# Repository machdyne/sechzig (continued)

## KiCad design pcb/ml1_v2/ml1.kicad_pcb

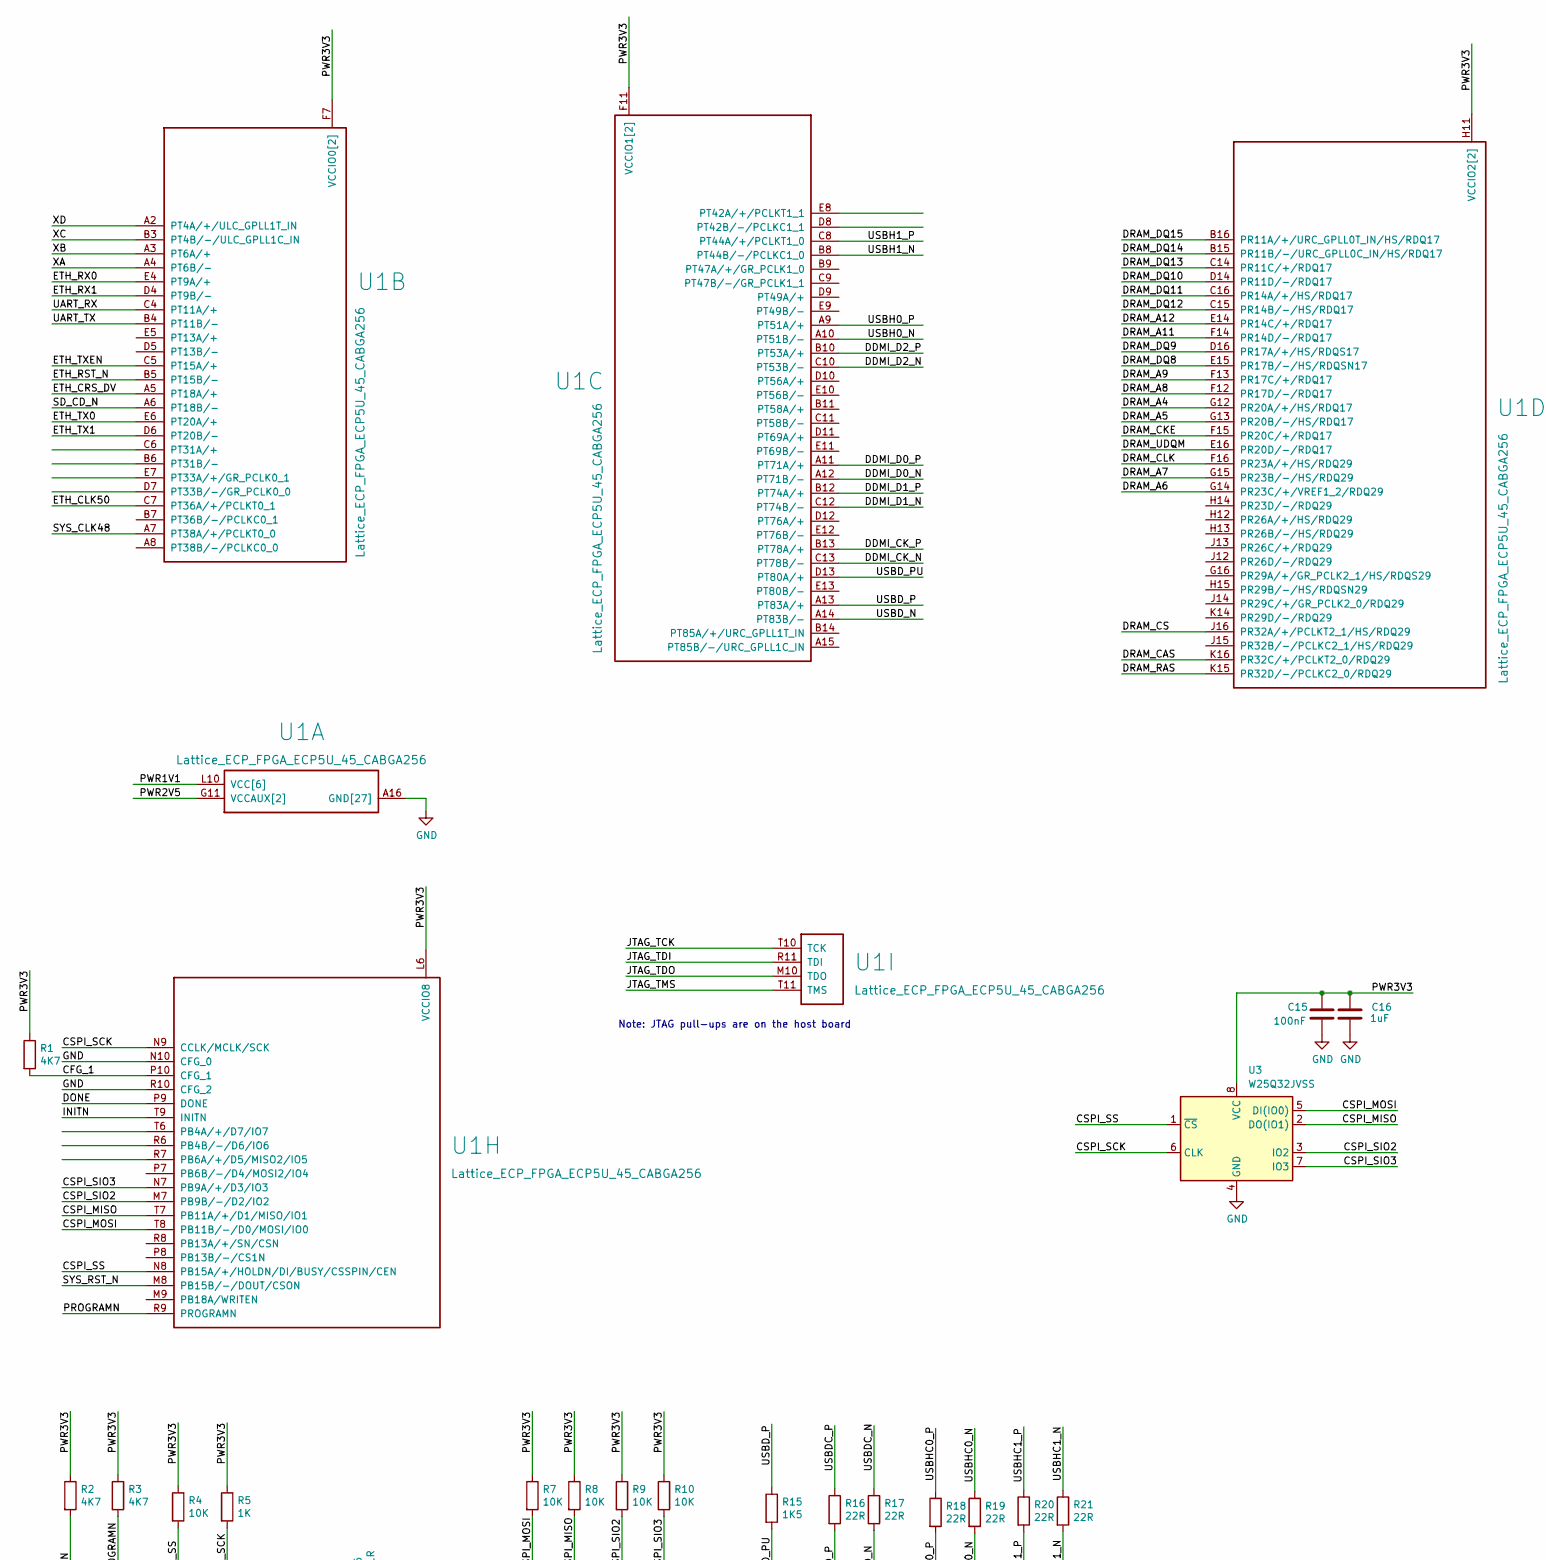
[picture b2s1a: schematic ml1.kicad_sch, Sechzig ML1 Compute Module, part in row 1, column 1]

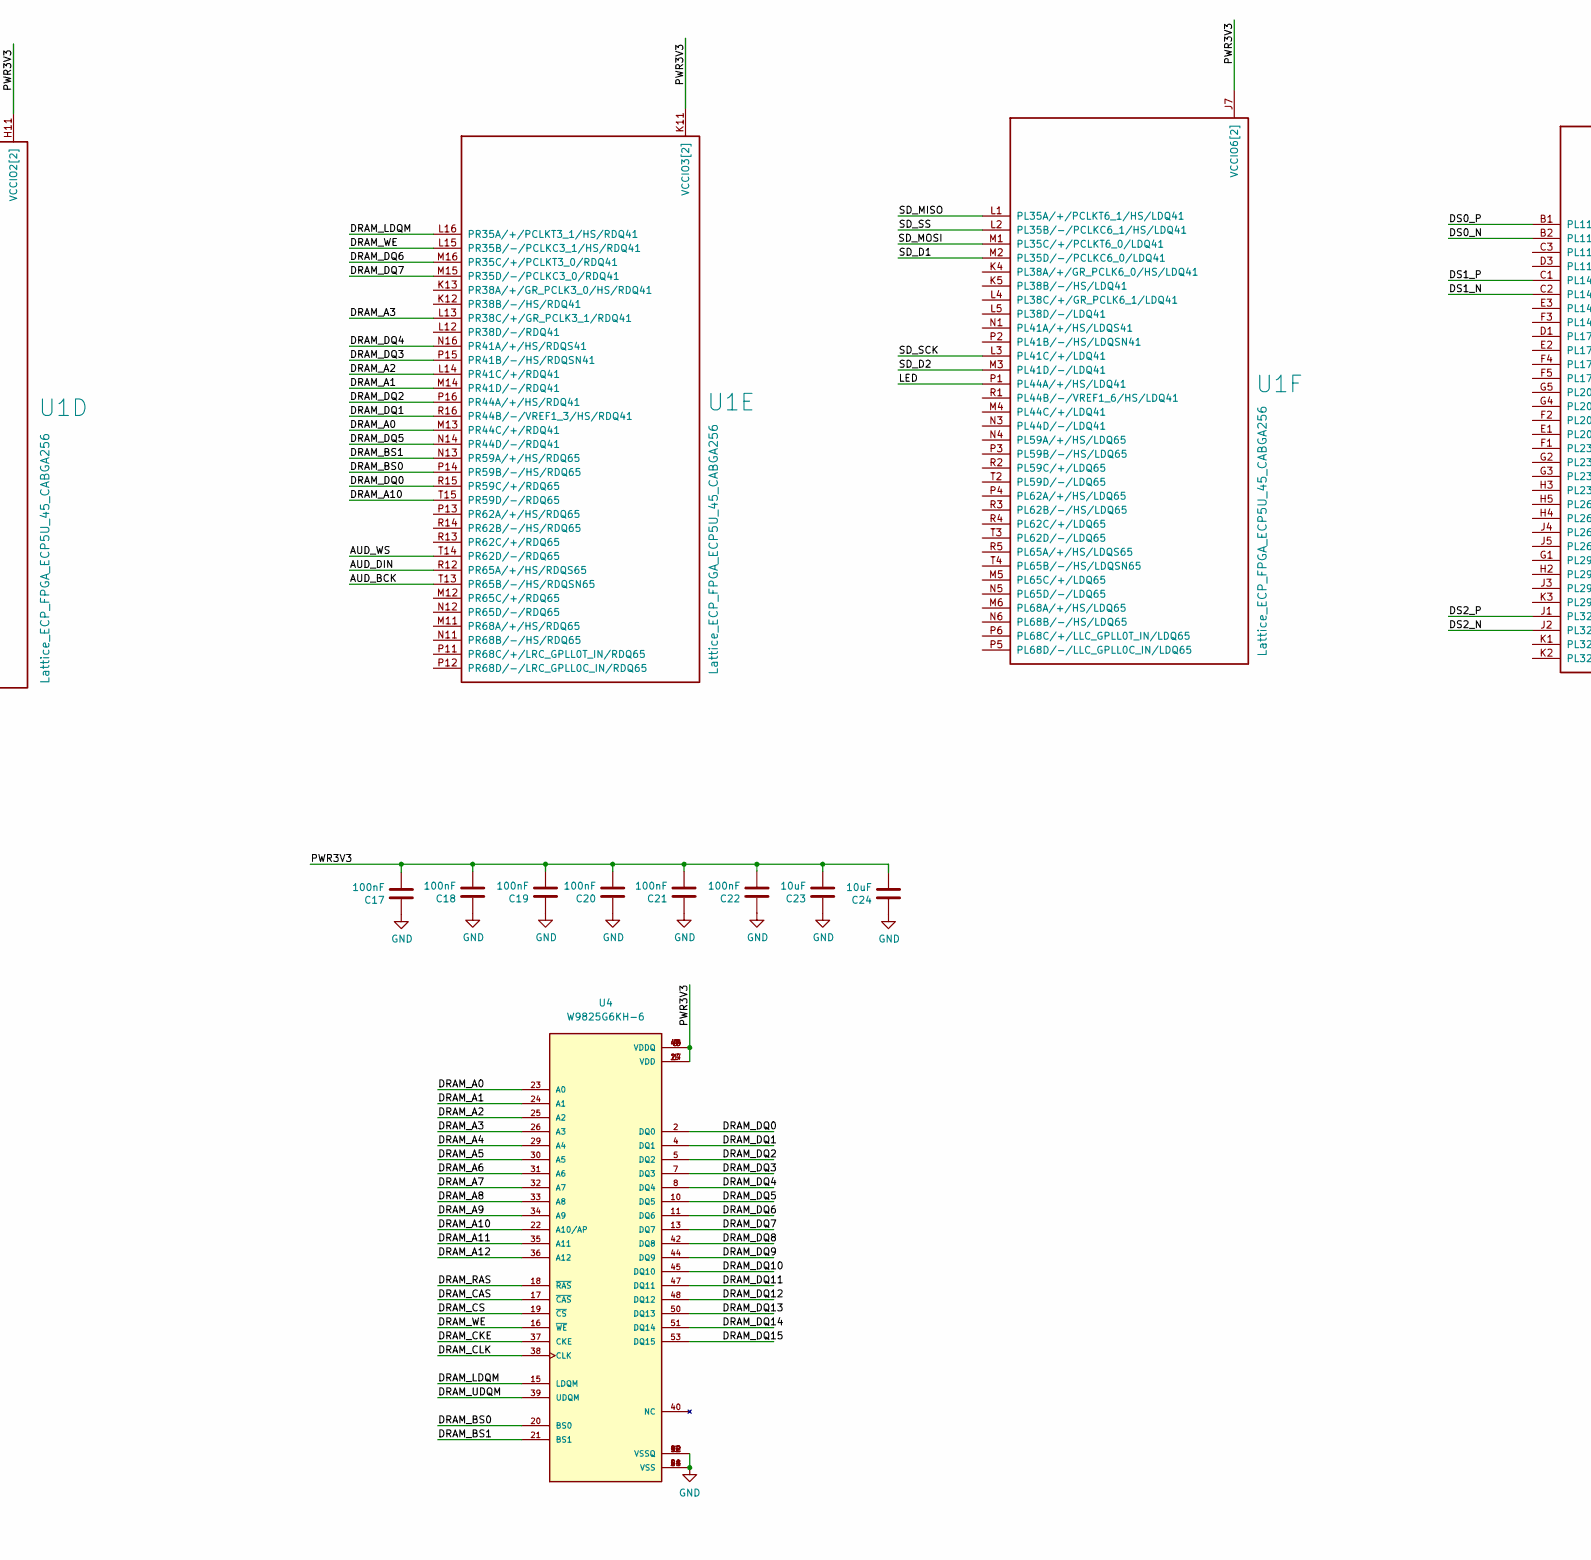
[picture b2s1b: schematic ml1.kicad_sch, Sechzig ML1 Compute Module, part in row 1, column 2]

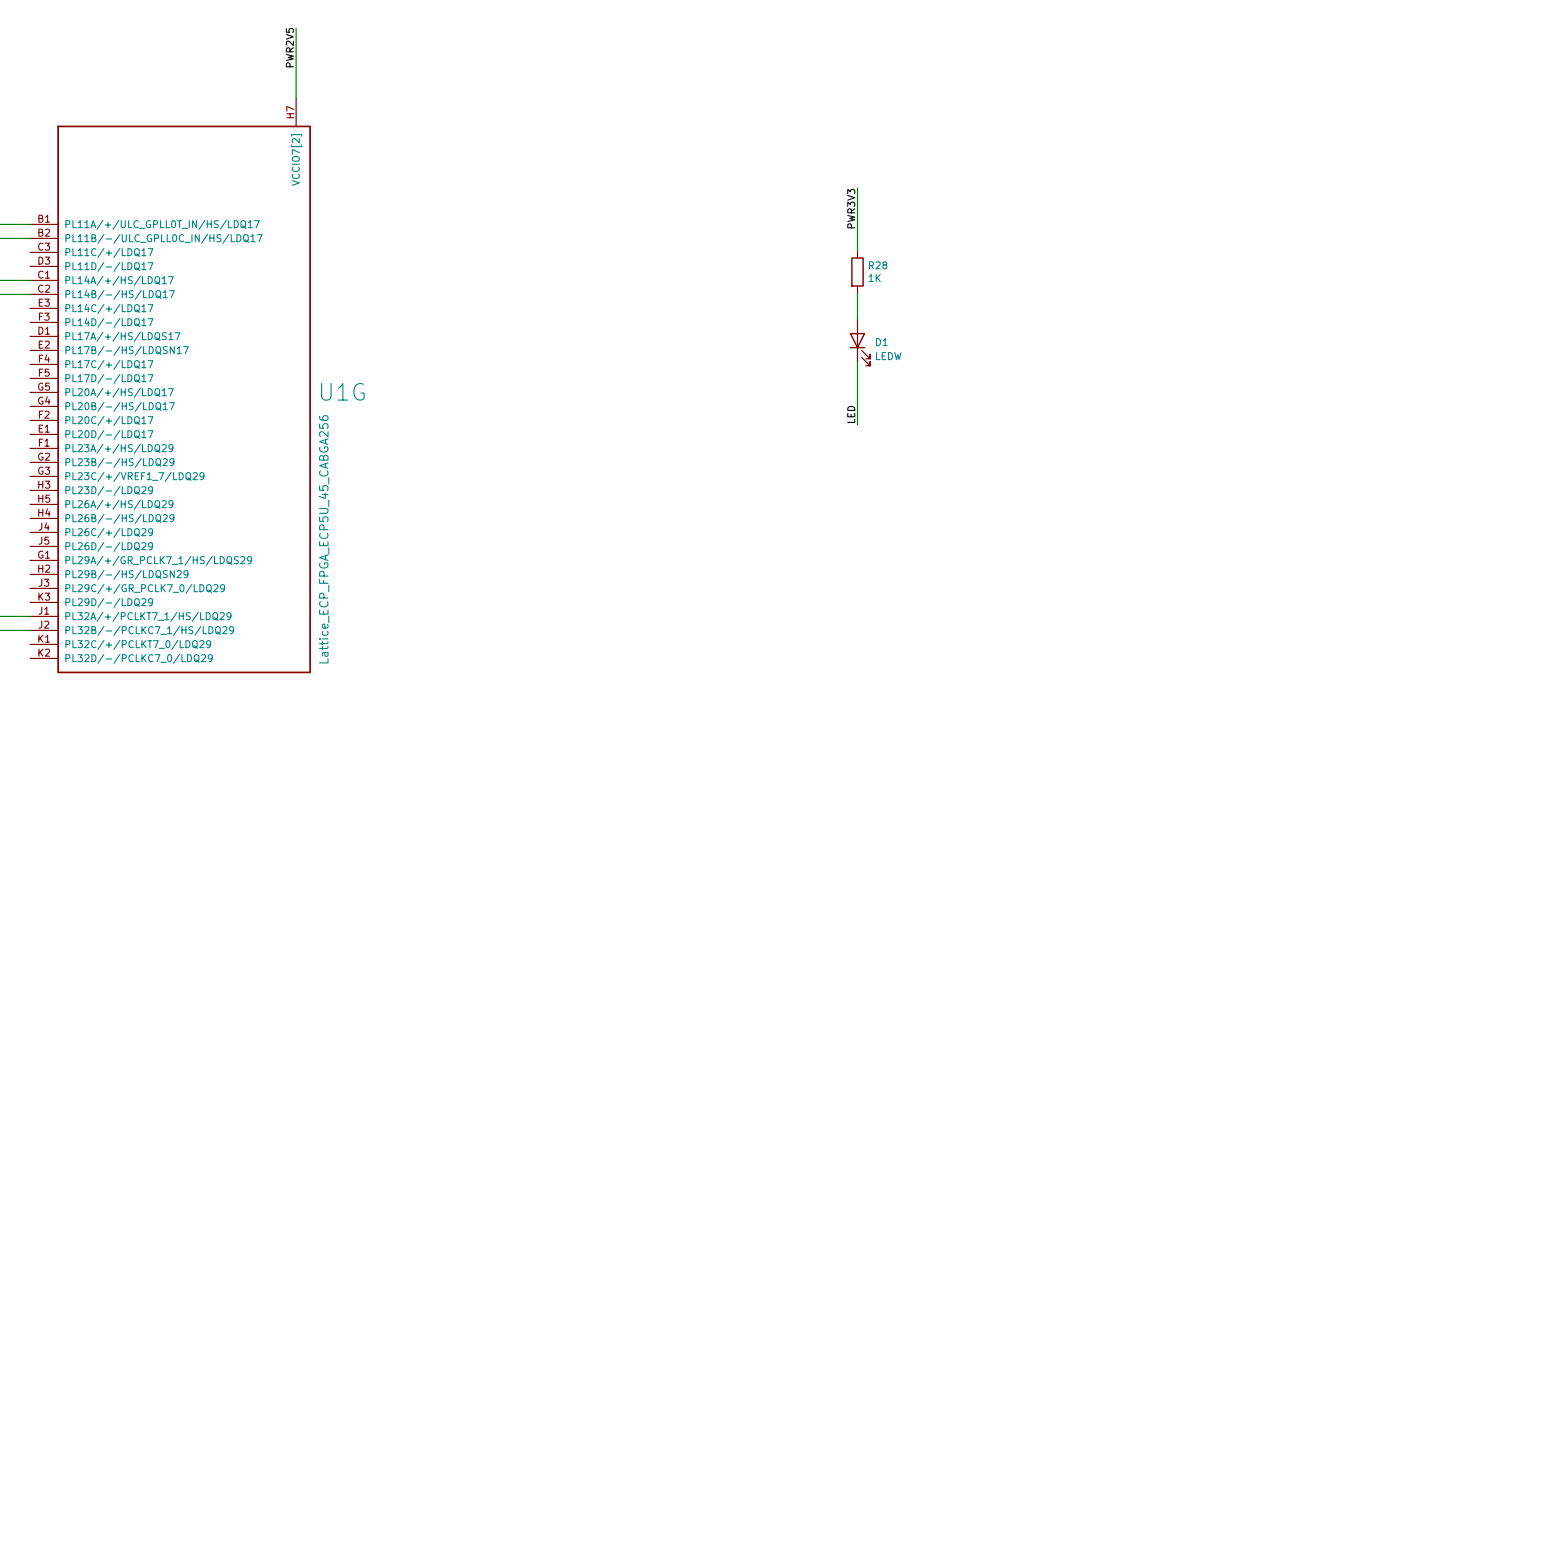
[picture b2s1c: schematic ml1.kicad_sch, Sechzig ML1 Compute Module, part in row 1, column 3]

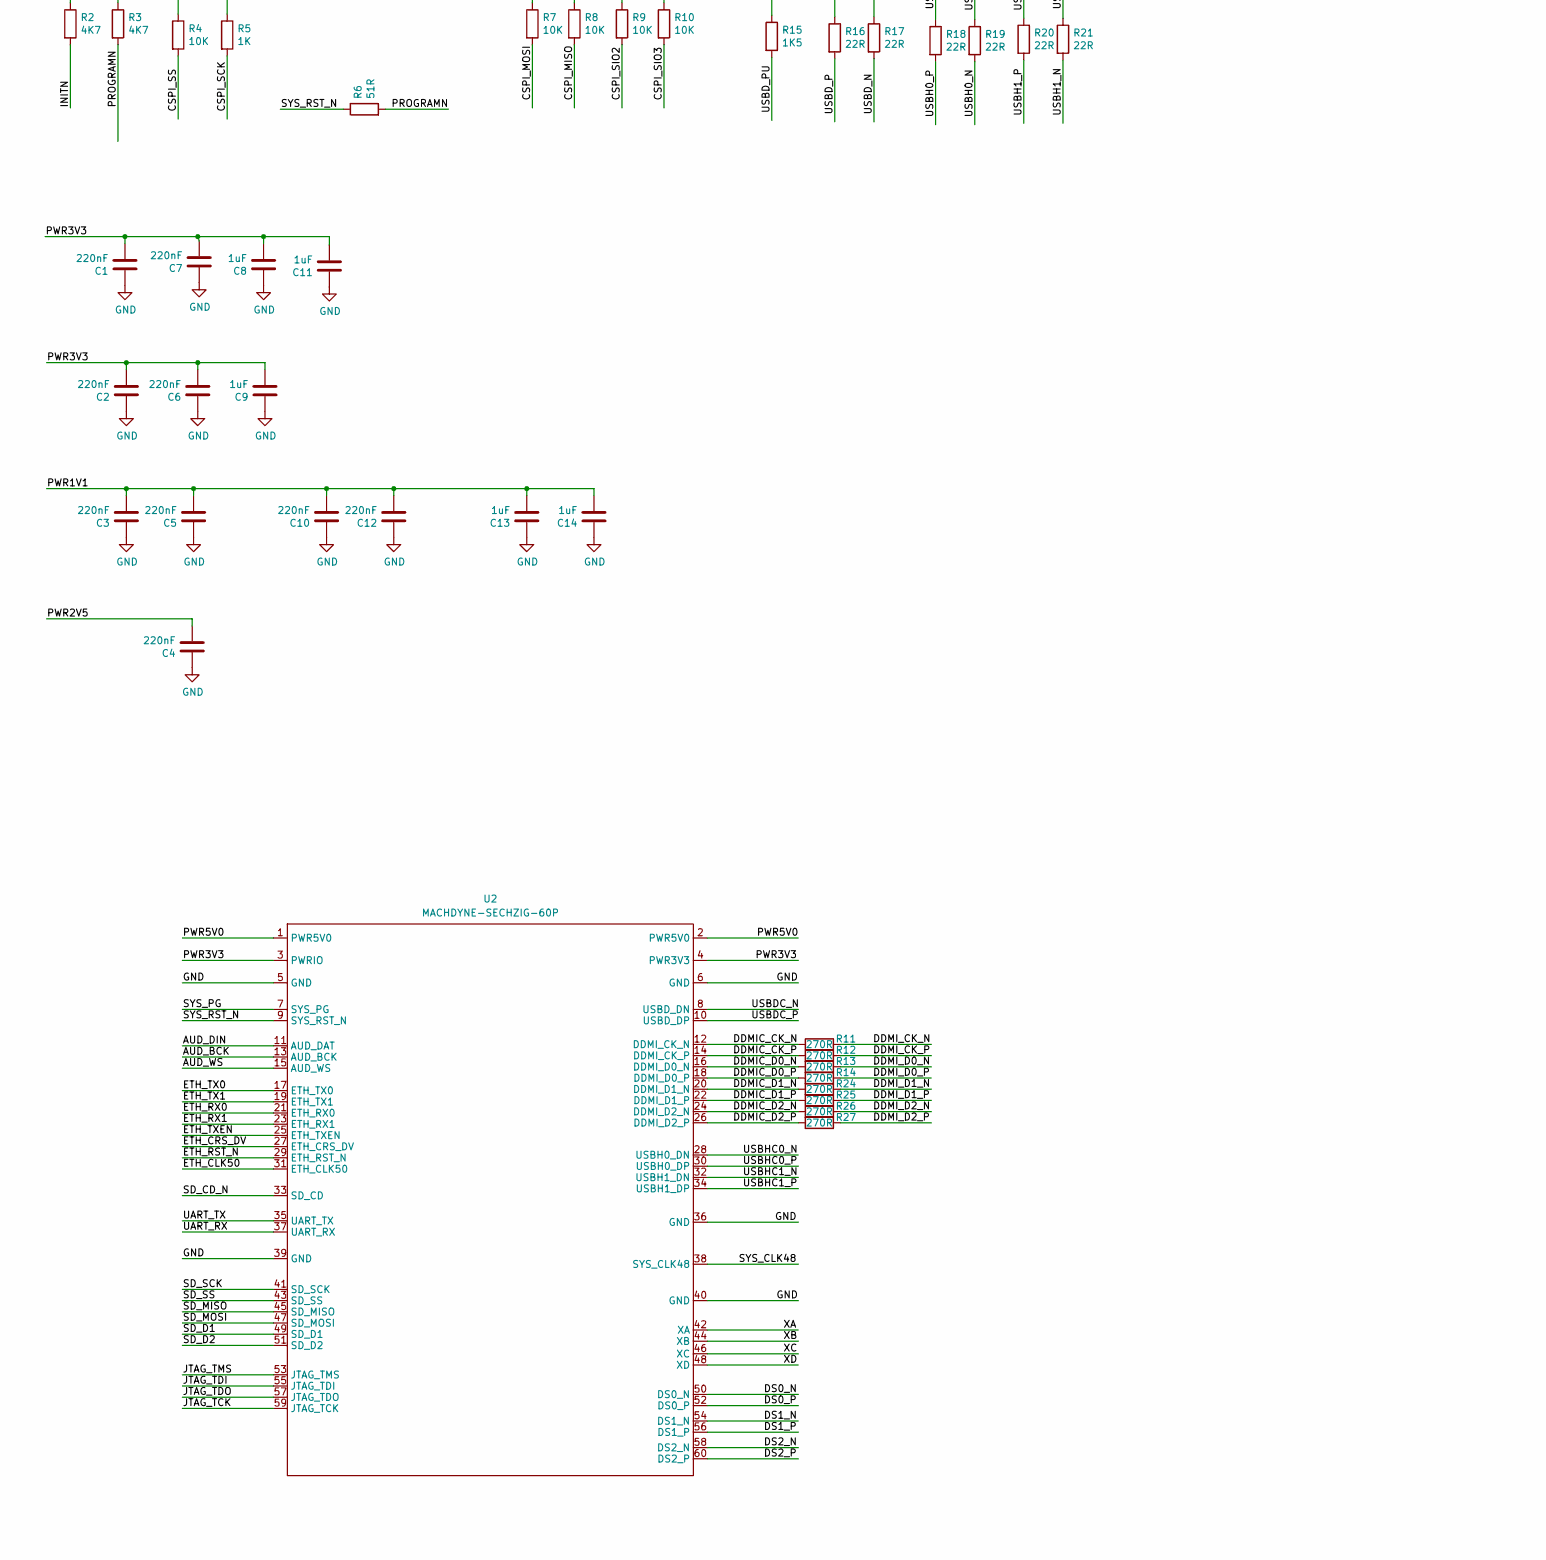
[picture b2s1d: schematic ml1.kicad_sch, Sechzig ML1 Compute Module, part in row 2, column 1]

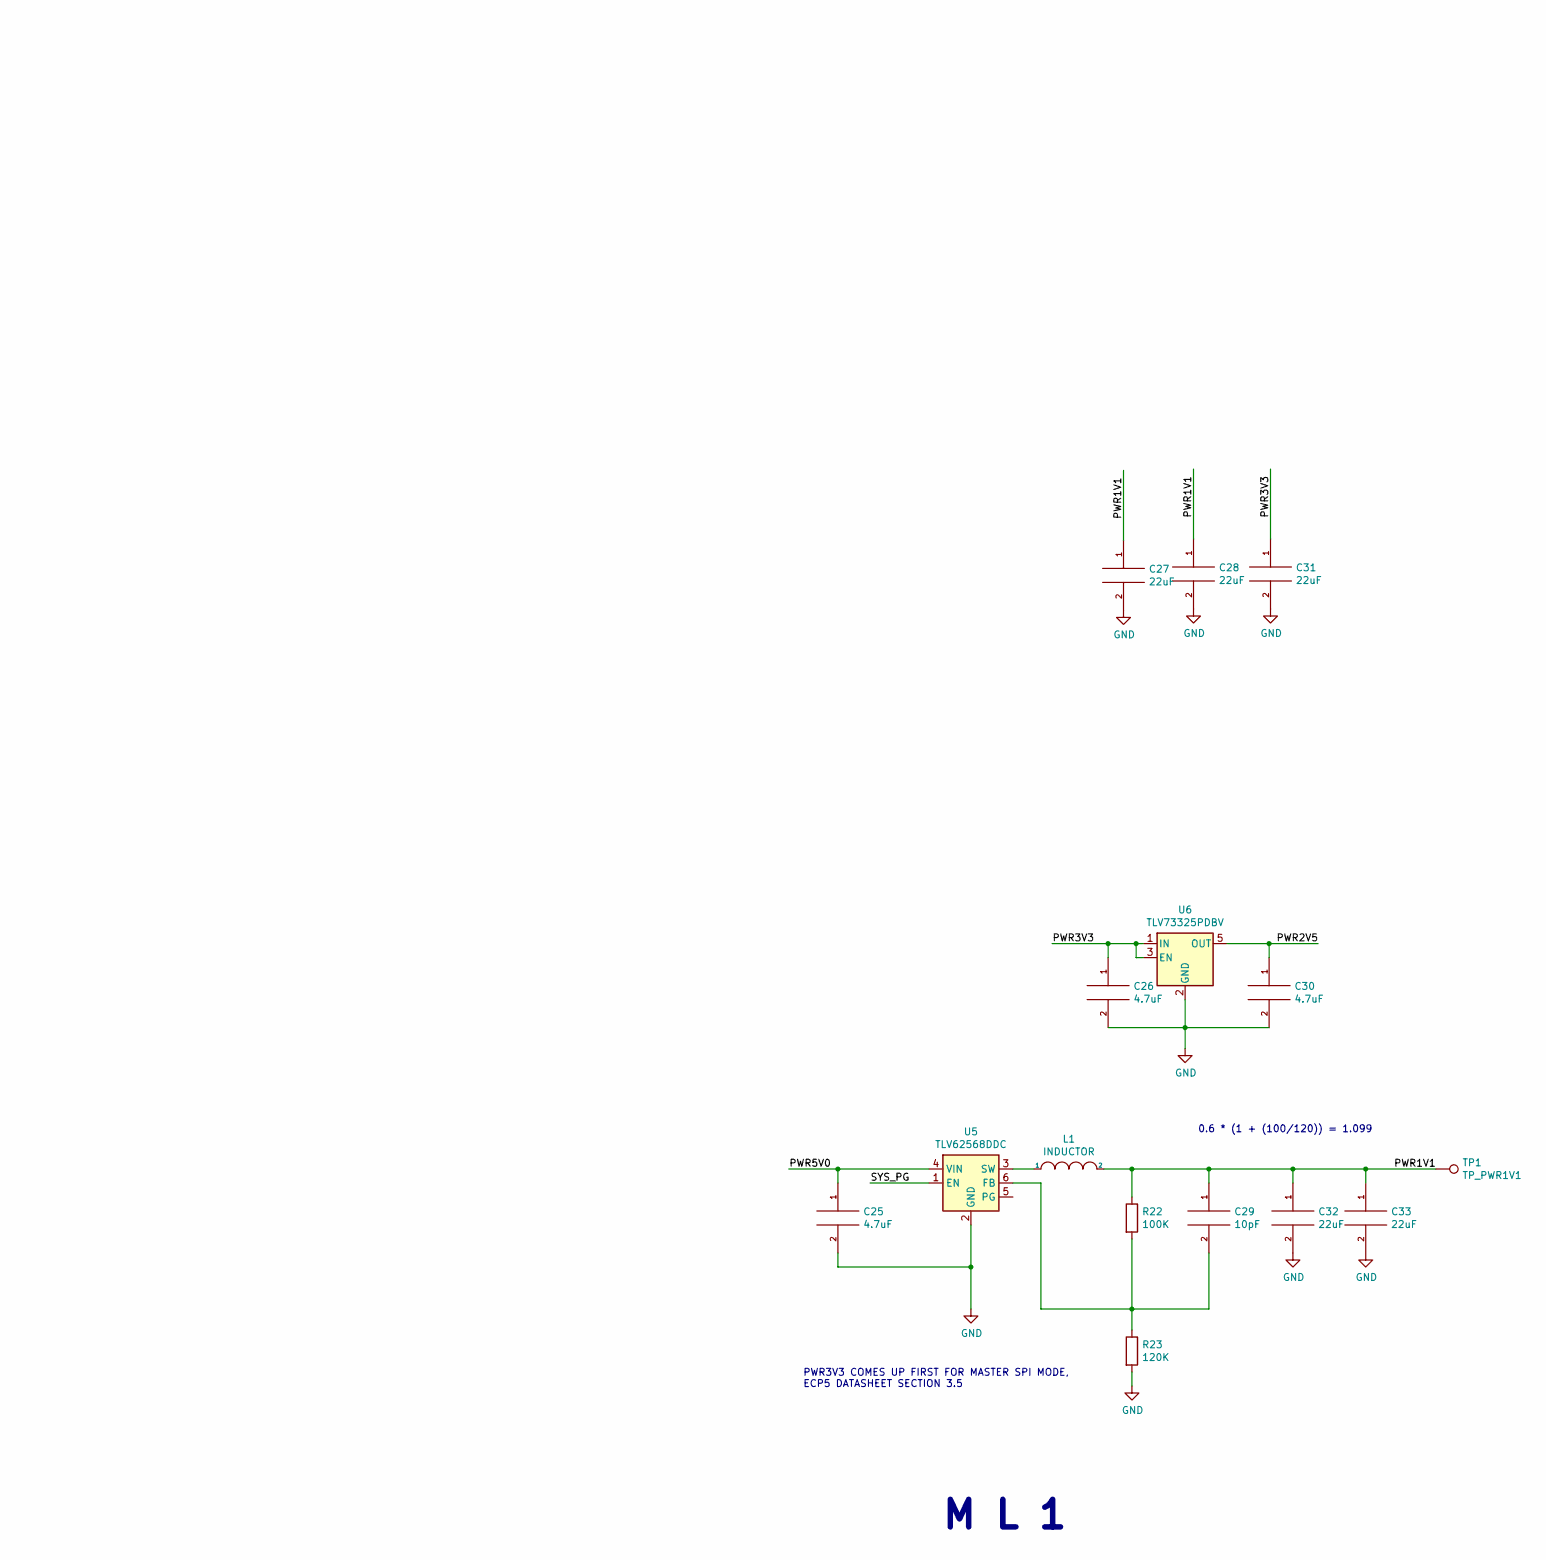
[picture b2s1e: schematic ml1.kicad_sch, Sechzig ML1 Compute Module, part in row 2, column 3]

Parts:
C1, C2, C3, C4, C5, C6, C7, C10, C12: 220nF; C_0603_1608Metric
C8, C9, C11, C13, C14, C16: 1uF; C_0603_1608Metric
C15, C17, C18, C19, C20, C21, C22: 100nF; C_0603_1608Metric
C23, C24: 10uF; C_0603_1608Metric
C25, C26, C30: 4.7uF; C_0603_1608Metric
C27, C28, C31, C32, C33: 22uF; C_0603_1608Metric
C29: 10pF; C_0603_1608Metric
D1: LEDW; LED_0603_1608Metric
L1: INDUCTOR; L_0805_2012Metric
R1, R2, R3: 4K7; R_0603_1608Metric
R4, R7, R8, R9, R10: 10K; R_0603_1608Metric
R5, R28: 1K; R_0603_1608Metric
R6: 51R; R_0603_1608Metric
R11, R12, R13, R14, R24, R25, R26, R27: 270R; R_0402_1005Metric
R15: 1K5; R_0402_1005Metric
R16, R17, R18, R19, R20, R21: 22R; R_0402_1005Metric
R22: 100K; R_0603_1608Metric
R23: 120K; R_0603_1608Metric
TP1: TP_PWR1V1; TestPoint_THTPad_D1.0mm_Drill0.5mm
U1: Lattice_ECP_FPGA_ECP5U_45_CABGA256; BGA-256_14.0x14.0mm_Layout16x16_P0.8mm_Ball0.45mm_Pad0.32mm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
U2: MACHDYNE-SECHZIG-60P; MACHDYNE_EDGE_60P
U3: W25Q32JVSS; SOIC-8_3.9x4.9mm_P1.27mm
U4: W9825G6KH-6; SOP80P1176X120-54N; PARTREV A05
U5: TLV62568DDC; SOT-23-6
U6: TLV73325PDBV; SOT-23-5

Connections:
/AUD_BCK: U1.T13 (PR65B/-/HS/RDQSN65), U2.13 (AUD_BCK)
/AUD_DIN: U1.R12 (PR65A/+/HS/RDQS65), U2.11 (AUD_DAT)
/AUD_WS: U1.T14 (PR62D/-/RDQ65), U2.15 (AUD_WS)
/CFG_1: R1.2, U1.P10 (CFG_1)
/CSPI_MISO: R8.2, U1.T7 (PB11A/+/D1/MISO/IO1), U3.2 (DO(IO1))
/CSPI_MOSI: R7.2, U1.T8 (PB11B/-/D0/MOSI/IO0), U3.5 (DI(IO0))
/CSPI_SCK: R5.2, U1.N9 (CCLK/MCLK/SCK), U3.6 (CLK)
/CSPI_SIO2: R9.2, U1.M7 (PB9B/-/D2/IO2), U3.3 (IO2)
/CSPI_SIO3: R10.2, U1.N7 (PB9A/+/D3/IO3), U3.7 (IO3)
/CSPI_SS: R4.2, U1.N8 (PB15A/+/HOLDN/DI/BUSY/CSSPIN/CEN), U3.1 (~CS)
/DDMIC_CK_N: R11.1, U2.12 (DDMI_CK_N)
/DDMIC_CK_P: R12.1, U2.14 (DDMI_CK_P)
/DDMIC_D0_N: R13.1, U2.16 (DDMI_D0_N)
/DDMIC_D0_P: R14.1, U2.18 (DDMI_D0_P)
/DDMIC_D1_N: R24.1, U2.20 (DDMI_D1_N)
/DDMIC_D1_P: R25.1, U2.22 (DDMI_D1_P)
/DDMIC_D2_N: R26.1, U2.24 (DDMI_D2_N)
/DDMIC_D2_P: R27.1, U2.26 (DDMI_D2_P)
/DDMI_CK_N: R11.2, U1.C13 (PT78B/-)
/DDMI_CK_P: R12.2, U1.B13 (PT78A/+)
/DDMI_D0_N: R13.2, U1.A12 (PT71B/-)
/DDMI_D0_P: R14.2, U1.A11 (PT71A/+)
/DDMI_D1_N: R24.2, U1.C12 (PT74B/-)
/DDMI_D1_P: R25.2, U1.B12 (PT74A/+)
/DDMI_D2_N: R26.2, U1.C10 (PT53B/-)
/DDMI_D2_P: R27.2, U1.B10 (PT53A/+)
/DONE: U1.P9 (DONE)
/DRAM_A0: U1.M13 (PR44C/+/RDQ41), U4.23 (A0)
/DRAM_A1: U1.M14 (PR41D/-/RDQ41), U4.24 (A1)
/DRAM_A2: U1.L14 (PR41C/+/RDQ41), U4.25 (A2)
/DRAM_A3: U1.L13 (PR38C/+/GR_PCLK3_1/RDQ41), U4.26 (A3)
/DRAM_A4: U1.G12 (PR20A/+/HS/RDQ17), U4.29 (A4)
/DRAM_A5: U1.G13 (PR20B/-/HS/RDQ17), U4.30 (A5)
/DRAM_A6: U1.G14 (PR23C/+/VREF1_2/RDQ29), U4.31 (A6)
/DRAM_A7: U1.G15 (PR23B/-/HS/RDQ29), U4.32 (A7)
/DRAM_A8: U1.F12 (PR17D/-/RDQ17), U4.33 (A8)
/DRAM_A9: U1.F13 (PR17C/+/RDQ17), U4.34 (A9)
/DRAM_A10: U1.T15 (PR59D/-/RDQ65), U4.22 (A10/AP)
/DRAM_A11: U1.F14 (PR14D/-/RDQ17), U4.35 (A11)
/DRAM_A12: U1.E14 (PR14C/+/RDQ17), U4.36 (A12)
/DRAM_BS0: U1.P14 (PR59B/-/HS/RDQ65), U4.20 (BS0)
/DRAM_BS1: U1.N13 (PR59A/+/HS/RDQ65), U4.21 (BS1)
/DRAM_CAS: U1.K16 (PR32C/+/PCLKT2_0/RDQ29), U4.17 (~CAS)
/DRAM_CKE: U1.F15 (PR20C/+/RDQ17), U4.37 (CKE)
/DRAM_CLK: U1.F16 (PR23A/+/HS/RDQ29), U4.38 (CLK)
/DRAM_CS: U1.J16 (PR32A/+/PCLKT2_1/HS/RDQ29), U4.19 (~CS)
/DRAM_DQ0: U1.R15 (PR59C/+/RDQ65), U4.2 (DQ0)
/DRAM_DQ1: U1.R16 (PR44B/-/VREF1_3/HS/RDQ41), U4.4 (DQ1)
/DRAM_DQ2: U1.P16 (PR44A/+/HS/RDQ41), U4.5 (DQ2)
/DRAM_DQ3: U1.P15 (PR41B/-/HS/RDQSN41), U4.7 (DQ3)
/DRAM_DQ4: U1.N16 (PR41A/+/HS/RDQS41), U4.8 (DQ4)
/DRAM_DQ5: U1.N14 (PR44D/-/RDQ41), U4.10 (DQ5)
/DRAM_DQ6: U1.M16 (PR35C/+/PCLKT3_0/RDQ41), U4.11 (DQ6)
/DRAM_DQ7: U1.M15 (PR35D/-/PCLKC3_0/RDQ41), U4.13 (DQ7)
/DRAM_DQ8: U1.E15 (PR17B/-/HS/RDQSN17), U4.42 (DQ8)
/DRAM_DQ9: U1.D16 (PR17A/+/HS/RDQS17), U4.44 (DQ9)
/DRAM_DQ10: U1.D14 (PR11D/-/RDQ17), U4.45 (DQ10)
/DRAM_DQ11: U1.C16 (PR14A/+/HS/RDQ17), U4.47 (DQ11)
/DRAM_DQ12: U1.C15 (PR14B/-/HS/RDQ17), U4.48 (DQ12)
/DRAM_DQ13: U1.C14 (PR11C/+/RDQ17), U4.50 (DQ13)
/DRAM_DQ14: U1.B15 (PR11B/-/URC_GPLL0C_IN/HS/RDQ17), U4.51 (DQ14)
/DRAM_DQ15: U1.B16 (PR11A/+/URC_GPLL0T_IN/HS/RDQ17), U4.53 (DQ15)
/DRAM_LDQM: U1.L16 (PR35A/+/PCLKT3_1/HS/RDQ41), U4.15 (LDQM)
/DRAM_RAS: U1.K15 (PR32D/-/PCLKC2_0/RDQ29), U4.18 (~RAS)
/DRAM_UDQM: U1.E16 (PR20D/-/RDQ17), U4.39 (UDQM)
/DRAM_WE: U1.L15 (PR35B/-/PCLKC3_1/HS/RDQ41), U4.16 (~WE)
/DS0_N: U1.B2 (PL11B/-/ULC_GPLL0C_IN/HS/LDQ17), U2.50 (DS0_N)
/DS0_P: U1.B1 (PL11A/+/ULC_GPLL0T_IN/HS/LDQ17), U2.52 (DS0_P)
/DS1_N: U1.C2 (PL14B/-/HS/LDQ17), U2.54 (DS1_N)
/DS1_P: U1.C1 (PL14A/+/HS/LDQ17), U2.56 (DS1_P)
/DS2_N: U1.J2 (PL32B/-/PCLKC7_1/HS/LDQ29), U2.58 (DS2_N)
/DS2_P: U1.J1 (PL32A/+/PCLKT7_1/HS/LDQ29), U2.60 (DS2_P)
/ETH_CLK50: U1.C7 (PT36A/+/PCLKT0_1), U2.31 (ETH_CLK50)
/ETH_CRS_DV: U1.A5 (PT18A/+), U2.27 (ETH_CRS_DV)
/ETH_RST_N: U1.B5 (PT15B/-), U2.29 (ETH_RST_N)
/ETH_RX0: U1.E4 (PT9A/+), U2.21 (ETH_RX0)
/ETH_RX1: U1.D4 (PT9B/-), U2.23 (ETH_RX1)
/ETH_TX0: U1.E6 (PT20A/+), U2.17 (ETH_TX0)
/ETH_TX1: U1.D6 (PT20B/-), U2.19 (ETH_TX1)
/ETH_TXEN: U1.C5 (PT15A/+), U2.25 (ETH_TXEN)
/INITN: R2.2, U1.T9 (INITN)
/JTAG_TCK: U1.T10 (TCK), U2.59 (JTAG_TCK)
/JTAG_TDI: U1.R11 (TDI), U2.55 (JTAG_TDI)
/JTAG_TDO: U1.M10 (TDO), U2.57 (JTAG_TDO)
/JTAG_TMS: U1.T11 (TMS), U2.53 (JTAG_TMS)
/LED: D1.1 (K), U1.P1 (PL44A/+/HS/LDQ41)
/PROGRAMN: R3.2, R6.2, U1.R9 (PROGRAMN)
/PWR1V1: C3.2, C5.2, C10.2, C12.2, C13.2, C14.2, C27.1, C28.1, C29.1, C32.1, C33.1, L1.2, R22.1, TP1.1, U1.G6 (VCC[6]), U1.G7 (VCC[6]), U1.G9 (VCC[6]), U1.L8 (VCC[6]), U1.L9 (VCC[6]), U1.L10 (VCC[6])
/PWR2V5: C4.2, C30.1, U1.G11 (VCCAUX[2]), U1.H6 (VCCIO7[2]), U1.H7 (VCCIO7[2]), U1.L7 (VCCAUX[2]), U6.5 (OUT)
/PWR3V3: C1.2, C2.2, C6.2, C7.2, C8.2, C9.2, C11.2, C15.1, C16.1, C17.2, C18.2, C19.2, C20.2, C21.2, C22.2, C23.2, C24.2, C26.1, C31.1, R1.1, R2.1, R3.1, R4.1, R5.1, R7.1, R8.1, R9.1, R10.1, R28.1, U1.F6 (VCCIO0[2]), U1.F7 (VCCIO0[2]), U1.F10 (VCCIO1[2]), U1.F11 (VCCIO1[2]), U1.H11 (VCCIO2[2]), U1.J6 (VCCIO6[2]), U1.J7 (VCCIO6[2]), U1.J11 (VCCIO2[2]), U1.K11 (VCCIO3[2]), U1.L6 (VCCIO8), U1.L11 (VCCIO3[2]), U2.3 (PWRIO), U2.4 (PWR3V3), U3.8 (VCC), U4.1 (VDD), U4.3 (VDDQ), U4.9 (VDDQ), U4.14 (VDD), U4.27 (VDD), U4.43 (VDDQ), U4.49 (VDDQ), U6.1 (IN), U6.3 (EN)
/PWR5V0: C25.1, U2.1 (PWR5V0), U2.2 (PWR5V0), U5.4 (VIN)
/SD_CD_N: U1.A6 (PT18B/-), U2.33 (SD_CD)
/SD_D1: U1.M2 (PL35D/-/PCLKC6_0/LDQ41), U2.49 (SD_D1)
/SD_D2: U1.M3 (PL41D/-/LDQ41), U2.51 (SD_D2)
/SD_MISO: U1.L1 (PL35A/+/PCLKT6_1/HS/LDQ41), U2.45 (SD_MISO)
/SD_MOSI: U1.M1 (PL35C/+/PCLKT6_0/LDQ41), U2.47 (SD_MOSI)
/SD_SCK: U1.L3 (PL41C/+/LDQ41), U2.41 (SD_SCK)
/SD_SS: U1.L2 (PL35B/-/PCLKC6_1/HS/LDQ41), U2.43 (SD_SS)
/SYS_CLK48: U1.A7 (PT38A/+/PCLKT0_0), U2.38 (SYS_CLK48)
/SYS_PG: U2.7 (SYS_PG), U5.1 (EN)
/SYS_RST_N: R6.1, U1.M8 (PB15B/-/DOUT/CSON), U2.9 (SYS_RST_N)
/UART_RX: U1.C4 (PT11A/+), U2.37 (UART_RX)
/UART_TX: U1.B4 (PT11B/-), U2.35 (UART_TX)
/USBDC_N: R17.1, U2.8 (USBD_DN)
/USBDC_P: R16.1, U2.10 (USBD_DP)
/USBD_N: R17.2, U1.A14 (PT83B/-)
/USBD_P: R15.1, R16.2, U1.A13 (PT83A/+)
/USBD_PU: R15.2, U1.D13 (PT80A/+)
/USBH0_N: R19.2, U1.A10 (PT51B/-)
/USBH0_P: R18.2, U1.A9 (PT51A/+)
/USBH1_N: R21.2, U1.B8 (PT44B/-/PCLKC1_0)
/USBH1_P: R20.2, U1.C8 (PT44A/+/PCLKT1_0)
/USBHC0_N: R19.1, U2.28 (USBH0_DN)
/USBHC0_P: R18.1, U2.30 (USBH0_DP)
/USBHC1_N: R21.1, U2.32 (USBH1_DN)
/USBHC1_P: R20.1, U2.34 (USBH1_DP)
/XA: U1.A4 (PT6B/-), U2.42 (XA)
/XB: U1.A3 (PT6A/+), U2.44 (XB)
/XC: U1.B3 (PT4B/-/ULC_GPLL1C_IN), U2.46 (XC)
/XD: U1.A2 (PT4A/+/ULC_GPLL1T_IN), U2.48 (XD)
GND: C1.1, C2.1, C3.1, C4.1, C5.1, C6.1, C7.1, C8.1, C9.1, C10.1, C11.1, C12.1, C13.1, C14.1, C15.2, C16.2, C17.1, C18.1, C19.1, C20.1, C21.1, C22.1, C23.1, C24.1, C25.2, C26.2, C27.2, C28.2, C30.2, C31.2, C32.2, C33.2, R23.2, U1.A1 (GND[27]), U1.A16 (GND[27]), U1.D2 (GND[27]), U1.D15 (GND[27]), U1.F8 (GND[27]), U1.F9 (GND[27]), U1.G8 (GND[27]), U1.G10 (GND[27]), U1.H1 (GND[27]), U1.H8 (GND[27]), U1.H9 (GND[27]), U1.H10 (GND[27]), U1.H16 (GND[27]), U1.J8 (GND[27]), U1.J9 (GND[27]), U1.J10 (GND[27]), U1.K6 (GND[27]), U1.K7 (GND[27]), U1.K8 (GND[27]), U1.K9 (GND[27]), U1.K10 (GND[27]), U1.N2 (GND[27]), U1.N10 (CFG_0), U1.N15 (GND[27]), U1.R10 (CFG_2), U1.T1 (GND[27]), U1.T5 (GND[27]), U1.T12 (GND[27]), U1.T16 (GND[27]), U2.5 (GND), U2.6 (GND), U2.36 (GND), U2.39 (GND), U2.40 (GND), U3.4 (GND), U4.6 (VSSQ), U4.12 (VSSQ), U4.28 (VSS), U4.41 (VSS), U4.46 (VSSQ), U4.52 (VSSQ), U4.54 (VSS), U5.2 (GND), U6.2 (GND)
unnamed: C29.2, R22.2, R23.1, U5.6 (FB)
unnamed: D1.2 (A), R28.2
unnamed: L1.1, U5.3 (SW)

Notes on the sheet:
M L 1
PWR3V3 COMES UP FIRST FOR MASTER SPI MODE, ECP5 DATASHEET SECTION 3.5
0.6 * (1 + (100/120)) = 1.099
Note: JTAG pull-ups are on the host board

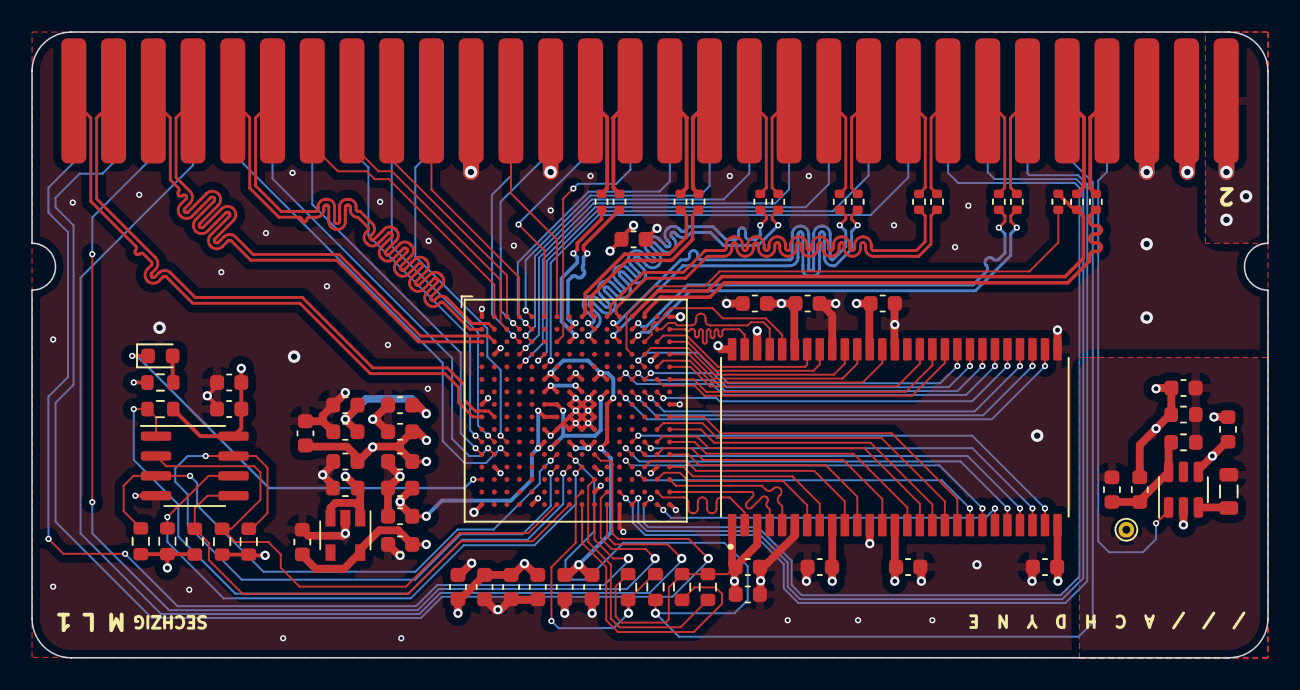
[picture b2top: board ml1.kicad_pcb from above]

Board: 4 copper layers, 79.0 x 40.0 mm, 70 parts (1 on the bottom side), 123 nets.
